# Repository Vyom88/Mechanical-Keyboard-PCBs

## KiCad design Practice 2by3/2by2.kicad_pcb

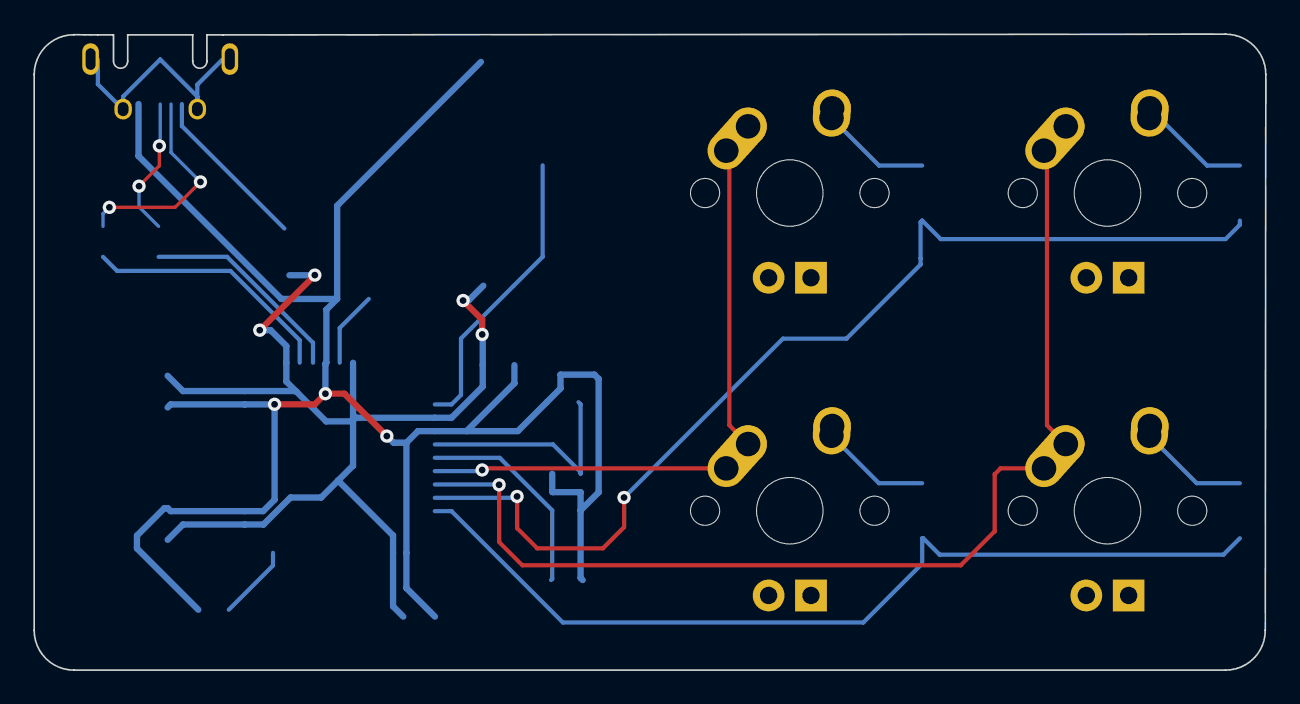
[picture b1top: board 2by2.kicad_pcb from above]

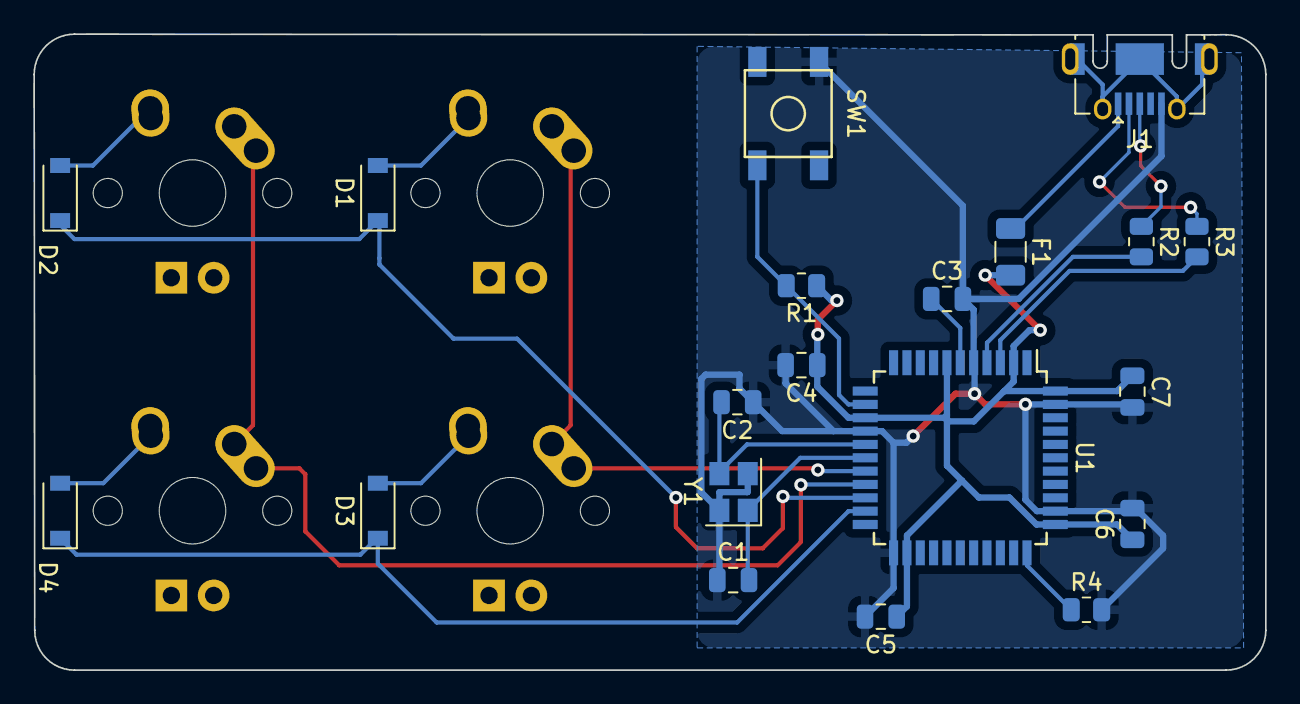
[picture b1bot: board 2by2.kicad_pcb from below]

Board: 2 copper layers, 73.9 x 38.1 mm, 24 parts (20 on the bottom side), 20 nets.

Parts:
C1, C2: 22pF; C_0805_2012Metric
C3: 1uF; C_0805_2012Metric
C4, C5, C6: 0.1uF; C_0805_2012Metric
C7: 10uF; C_0805_2012Metric
D1, D2, D3, D4: D_Small; D_SOD-123
F1: 500mA; Fuse_1206_3216Metric
J1: USB_B_Micro; USB_Micro-AB_Molex_47590-0001
MX1, MX2, MX3, MX4: MX-NoLED; MX-1U
R1, R4: 10k; R_0805_2012Metric
R2, R3: 22; R_0805_2012Metric
SW1: SW_Push; SKQG-1155865
U1: ATmega32U4-A; TQFP-44_10x10mm_P0.8mm
Y1: 16MHz; Crystal_SMD_3225-4Pin_3.2x2.5mm

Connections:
+5V: C4.1, C5.1, C6.1, C7.1, F1.2, R1.1, U1.2 (UVCC), U1.7 (VBUS), U1.14 (VCC), U1.24 (AVCC), U1.34 (VCC), U1.44 (AVCC)
/COL 0: MX1.1 (COL), MX3.1 (COL), U1.18 (PD0)
/COL 1: MX2.1 (COL), MX4.1 (COL), U1.19 (PD1)
/D+: J1.3 (D+), R2.1
/D-: J1.2 (D-), R3.1
/ROW 0: D1.1 (K), D2.1 (K), U1.20 (PD2)
/ROW 1: D3.1 (K), D4.1 (K), U1.21 (PD3)
GND: C1.1, C2.1, C3.2, C4.2, C5.2, C6.2, C7.2, J1.5 (GND), R4.2, SW1.1, U1.5 (UGND), U1.15 (GND), U1.23 (GND), U1.35 (GND), U1.43 (GND), Y1.2, Y1.4
unnamed: C1.2, U1.17 (XTAL1), Y1.1
unnamed: C2.2, U1.16 (XTAL2), Y1.3
unnamed: C3.1, U1.6 (UCAP)
unnamed: D1.2 (A), MX1.2 (ROW)
unnamed: D2.2 (A), MX2.2 (ROW)
unnamed: D3.2 (A), MX3.2 (ROW)
unnamed: D4.2 (A), MX4.2 (ROW)
unnamed: R1.2, SW1.2, U1.13 (~RESET)
unnamed: R2.2, U1.4 (D+)
unnamed: R3.2, U1.3 (D-)
unnamed: R4.1, U1.33 (~HWB/PE2)
VCC: F1.1, J1.1 (VBUS)

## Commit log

2023-11-18 Added PCBs
2023-11-19 Deleted unnecessary files
2023-11-19 Deleting Unnecessary Files
